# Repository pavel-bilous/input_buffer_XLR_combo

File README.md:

# Input buffer for amplifier with balanced inputs

This buffer serves as an impedance matching and is implemented on the board that allows for balanced XLR inputs for two channels.

## PCB rendered in 3d:

## Schematics:

Inputs are ESD protected with bidirectional TVS diodes. Not required, but nice to have. 

Opamps can be NE5532 or LM4562 or any other with good unity gain stability. 

Input XLR connectors are Neutrik NCJ6FA-H.

Capacitors for input low pass filters are C0G or NP0 type. Decoupling capacitors are X7R 100nF or higher (1uF - 10uF will work great).

## PCB layout:

Bottom layer is GND. Top layer is signal + power and GND poured in between. Stiching vias are then applied to connect bottom and top GND planes to ensure those are as close to 0 as possible.

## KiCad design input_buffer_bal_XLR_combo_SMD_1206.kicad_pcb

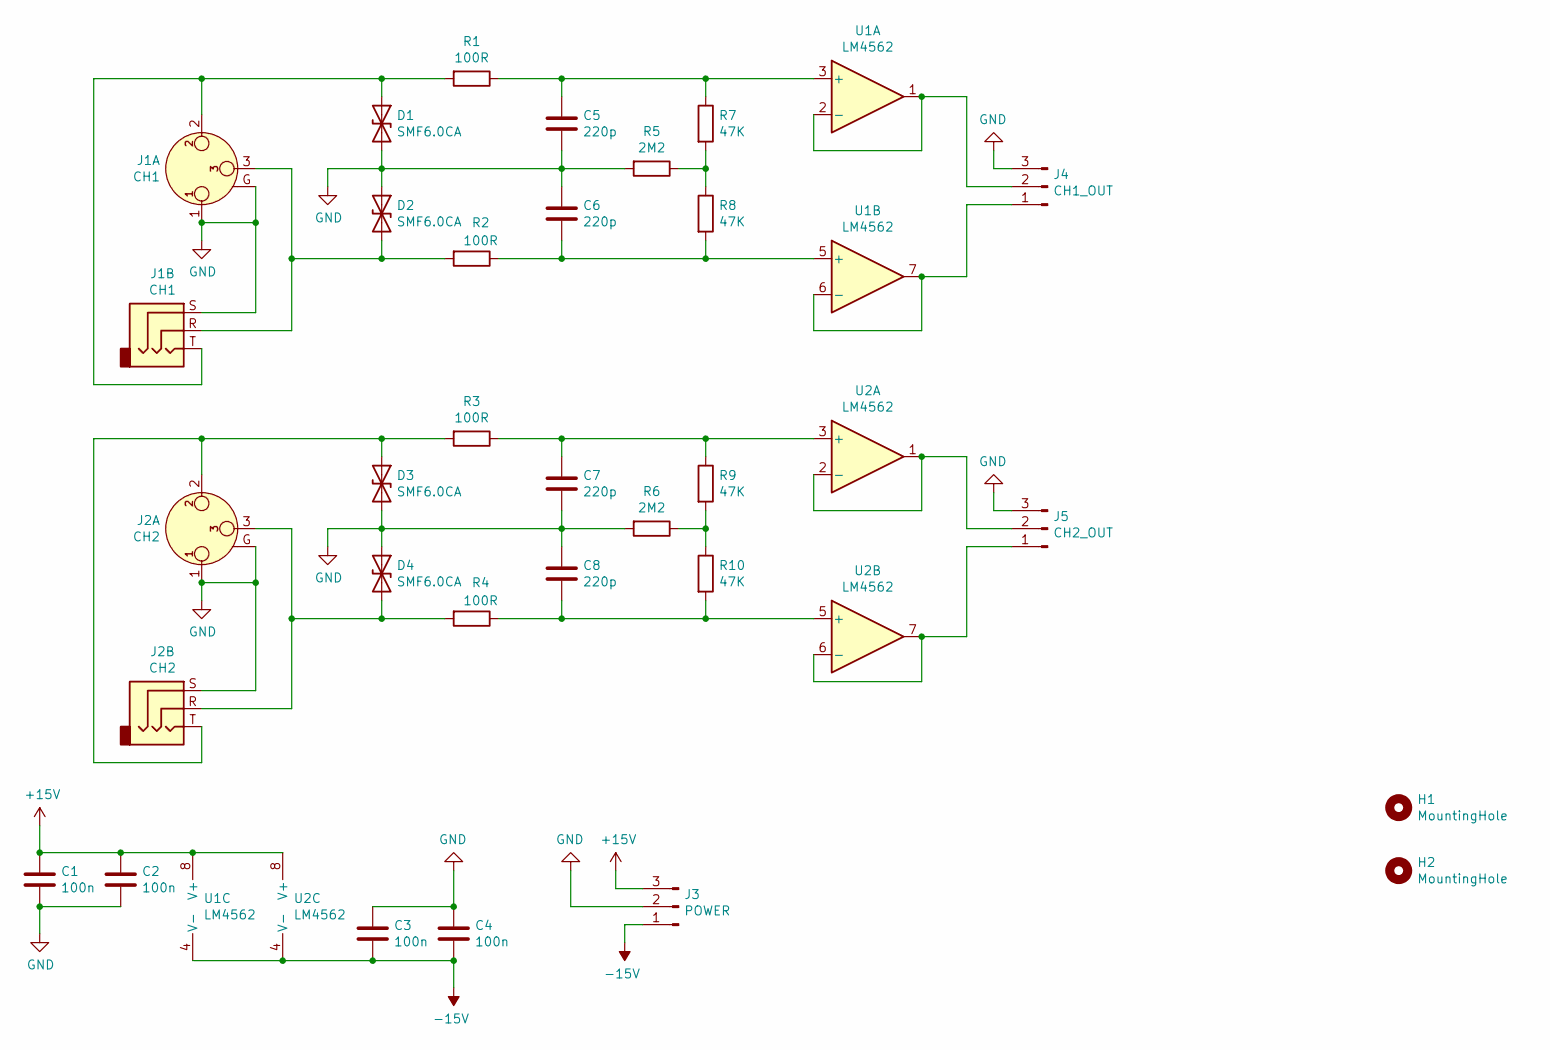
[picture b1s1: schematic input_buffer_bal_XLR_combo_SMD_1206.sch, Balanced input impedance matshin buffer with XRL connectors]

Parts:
C1, C2, C3, C4: 100n; C_1206_3216Metric_Pad1.42x1.75mm_HandSolder
C5, C6, C7, C8: 220p; C_1206_3216Metric_Pad1.42x1.75mm_HandSolder
D1, D2, D3, D4: SMF6.0CA; D_SOD-123F
H1, H2: MountingHole; MountingHole_3.5mm_Pad_Via
J1: CH1; Jack_XLR-6.35mm_Neutrik_NCJ6FA-H-0_Horizontal
J2: CH2; Jack_XLR-6.35mm_Neutrik_NCJ6FA-H-0_Horizontal
J3: POWER; TerminalBlock_ Amphenol_01_03_P3.50mm
J4: CH1_OUT; TerminalBlock_ Amphenol_01_03_P3.50mm
J5: CH2_OUT; TerminalBlock_ Amphenol_01_03_P3.50mm
R1, R2, R3, R4: 100R; R_1206_3216Metric
R5, R6: 2M2; R_1206_3216Metric
R7, R8, R9, R10: 47K; R_1206_3216Metric
U1, U2: LM4562; SOIC-8_3.9x4.9mm_P1.27mm

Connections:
+15V: C1.1, C2.1, J3.3, U1.8 (V+), U2.8 (V+)
-15V: C3.2, C4.2, J3.1, U1.4 (V-), U2.4 (V-)
GND: C1.2, C2.2, C3.1, C4.1, C5.2, C6.1, C7.2, C8.1, D1.2 (A2), D2.1 (A1), D3.2 (A2), D4.1 (A1), J1.1, J1.G, J1.S, J2.1, J2.G, J2.S, J3.2, J4.3, J5.3, R5.2, R6.2
unnamed: C5.1, R1.1, R7.1, U1.3 (+)
unnamed: C6.2, R2.1, R8.2, U1.5 (+)
unnamed: C7.1, R3.1, R9.1, U2.3 (+)
unnamed: C8.2, R4.1, R10.2, U2.5 (+)
unnamed: D1.1 (A1), J1.2, J1.T, R1.2
unnamed: D2.2 (A2), J1.3, J1.R, R2.2
unnamed: D3.1 (A1), J2.2, J2.T, R3.2
unnamed: D4.2 (A2), J2.3, J2.R, R4.2
unnamed: J4.1, U1.6 (-), U1.7
unnamed: J4.2, U1.1, U1.2 (-)
unnamed: J5.1, U2.6 (-), U2.7
unnamed: J5.2, U2.1, U2.2 (-)
unnamed: R5.1, R7.2, R8.1
unnamed: R6.1, R9.2, R10.1

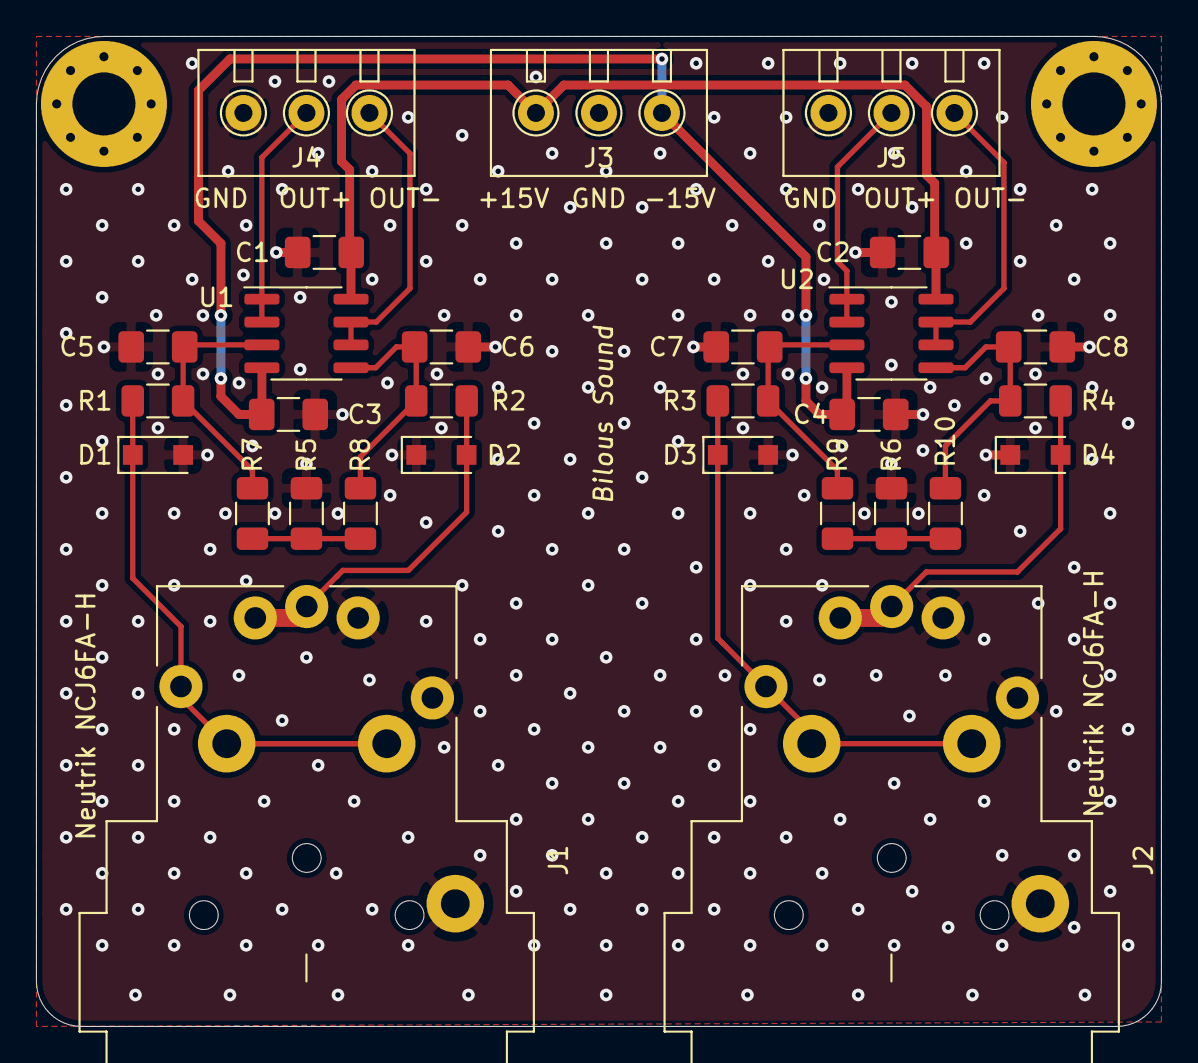
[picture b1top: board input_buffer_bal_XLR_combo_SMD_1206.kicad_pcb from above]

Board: 2 copper layers, 62.5 x 55.0 mm, 31 parts (0 on the bottom side), 17 nets.

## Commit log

2023-04-13 generated gerbers
2023-04-15 Changed footprint for TVS diodes to DFN1006
2023-04-15 added 3d and pcb images
2023-04-15 updated TVS diode
2023-04-15 added files for THT version of the project
2023-04-15 cleared img and gerber directories
2023-05-04 minor improvements
2023-05-05 minor fixes
